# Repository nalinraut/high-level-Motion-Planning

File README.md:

Contributors: GUnnar Horve | Max Merlin | Nishant Doshi | Prakash Bhaskaran | Self.
#IML Internal Repository

by CIBR Lab @ WPI

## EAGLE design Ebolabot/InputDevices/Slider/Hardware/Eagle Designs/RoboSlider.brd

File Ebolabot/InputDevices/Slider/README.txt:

The RoboSlider provides for reading and commanding the position of audio sliders
and buttons, and is specialized for the control of the joint angles any 7 DOF robot.
	*  slider.py -- communicates with RoboSlider devices, allowing for reading and
	   writing slider positions and button states. Also provides easy methods for
	   mapping input and output.
	*  /slider_driver -- contains the Arduino code (and dependent files) for the low
	   level controls of the slider, and for messaging with the computer.
	*  /Hardware -- contains the PCB and enclosure designs for the most recent slider
	   design, and includes a detailed Bill of Materials with links to suppliers.
	*  baxter_slider.py -- utilized the slider module to control Baxter's joint angles
	   with absolute positioning between the slider and Baxter.

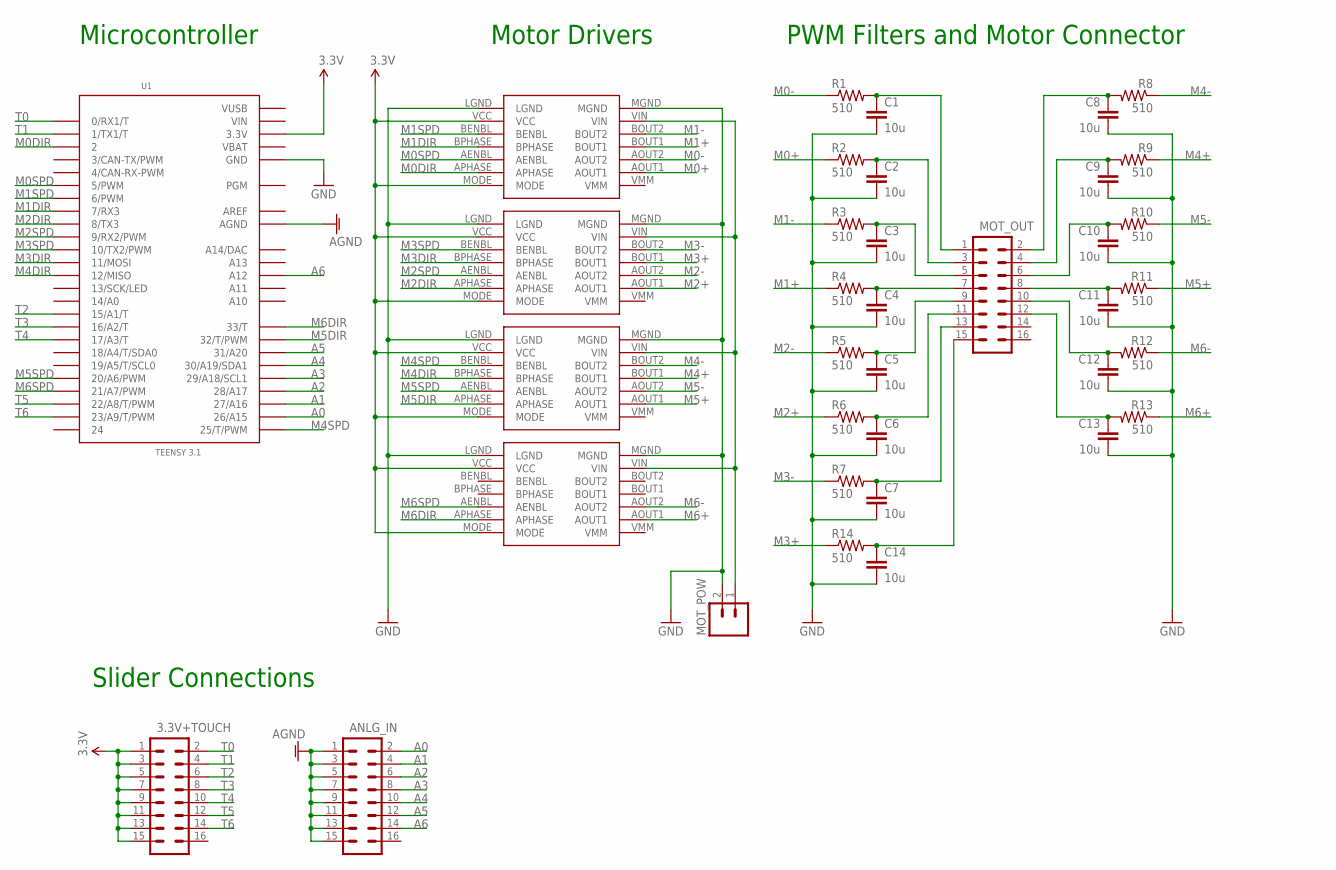
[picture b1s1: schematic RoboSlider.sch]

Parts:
3.3V+TOUCH: M08X2; 2X8
ANLG_IN: M08X2; 2X8
C1, C2, C3, C4, C5, C6, C7, C8, C9, C10, C11, C12, C13, C14: 10u; CAP-PTH-SMALL
MOT_OUT: M08X2; 2X8
MOT_POW: M02PTH; 1X02
R1, R2, R3, R4, R5, R6, R7, R8, R9, R10, R11, R12, R13, R14: 510; AXIAL-0.3
U1: TEENSY 3.1; TEENSY_3.1_ALLPINS
U$1, U$2, U$3, U$4: POLOLU_MOTOR_DRV8835THROUGHHOLE; POLOLU_MOTOR_DRV_DRV8835

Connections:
3.3V: 3.3V+TOUCH.1, 3.3V+TOUCH.3, 3.3V+TOUCH.5, 3.3V+TOUCH.7, 3.3V+TOUCH.9, 3.3V+TOUCH.11, 3.3V+TOUCH.13, 3.3V+TOUCH.15, U1.3.3V, U1.3.3V1 (3.3V), U1.3.3V2 (3.3V), U$1.MODE, U$1.VCC, U$2.MODE, U$2.VCC, U$3.MODE, U$3.VCC, U$4.MODE, U$4.VCC
9V: MOT_POW.1, U$1.VIN, U$2.VIN, U$3.VIN, U$4.VIN
A0: ANLG_IN.2, U1.26 (26/A15)
A1: ANLG_IN.4, U1.27 (27/A16)
A2: ANLG_IN.6, U1.28 (28/A17)
A3: ANLG_IN.8, U1.29 (29/A18/SCL1)
A4: ANLG_IN.10, U1.30 (30/A19/SDA1)
A5: ANLG_IN.12, U1.31 (31/A20)
A6: ANLG_IN.14, U1.A12
AGND: ANLG_IN.1, ANLG_IN.3, ANLG_IN.5, ANLG_IN.7, ANLG_IN.9, ANLG_IN.11, ANLG_IN.13, ANLG_IN.15, U1.AGND
AREF: U1.AREF
GND: C1.2, C2.2, C3.2, C4.2, C5.2, C6.2, C7.2, C8.2, C9.2, C10.2, C11.2, C12.2, C13.2, C14.2, MOT_POW.2, U1.GND, U1.GND1 (GND), U1.GND2 (GND), U$1.LGND, U$1.MGND, U$2.LGND, U$2.MGND, U$3.LGND, U$3.MGND, U$4.LGND, U$4.MGND
M0+: R2.P$1 (1), U$1.AOUT1
M0-: R1.P$1 (1), U$1.AOUT2
M0DIR: U1.2, U$1.APHASE
M0SPD: U1.5 (5/PWM), U$1.AENBL
M1+: R4.P$1 (1), U$1.BOUT1
M1-: R3.P$1 (1), U$1.BOUT2
M1DIR: U1.7 (7/RX3), U$1.BPHASE
M1SPD: U1.6 (6/PWM), U$1.BENBL
M2+: R6.P$1 (1), U$2.AOUT1
M2-: R5.P$1 (1), U$2.AOUT2
M2DIR: U1.8 (8/TX3), U$2.APHASE
M2SPD: U1.9 (9/RX2/PWM), U$2.AENBL
M3+: R14.P$1 (1), U$2.BOUT1
M3-: R7.P$1 (1), U$2.BOUT2
M3DIR: U1.11 (11/MOSI), U$2.BPHASE
M3SPD: U1.10 (10/TX2/PWM), U$2.BENBL
M4+: R9.P$1 (1), U$3.BOUT1
M4-: R8.P$1 (1), U$3.BOUT2
M4DIR: U1.12 (12/MISO), U$3.BPHASE
M4SPD: U1.25 (25/T/PWM), U$3.BENBL
M5+: R11.P$1 (1), U$3.AOUT1
M5-: R10.P$1 (1), U$3.AOUT2
M5DIR: U1.32 (32/T/PWM), U$3.APHASE
M5SPD: U1.20/A6 (20/A6/PWM), U$3.AENBL
M6+: R13.P$1 (1), U$4.AOUT1
M6-: R12.P$1 (1), U$4.AOUT2
M6DIR: U1.33 (33/T), U$4.APHASE
M6SPD: U1.21/A7 (21/A7/PWM), U$4.AENBL
unnamed: C1.1, MOT_OUT.1, R1.P$2 (2)
unnamed: C2.1, MOT_OUT.3, R2.P$2 (2)
unnamed: C3.1, MOT_OUT.5, R3.P$2 (2)
unnamed: C4.1, MOT_OUT.7, R4.P$2 (2)
unnamed: C5.1, MOT_OUT.9, R5.P$2 (2)
unnamed: C6.1, MOT_OUT.11, R6.P$2 (2)
unnamed: C7.1, MOT_OUT.13, R7.P$2 (2)
unnamed: C8.1, MOT_OUT.2, R8.P$2 (2)
unnamed: C9.1, MOT_OUT.4, R9.P$2 (2)
unnamed: C10.1, MOT_OUT.6, R10.P$2 (2)
unnamed: C11.1, MOT_OUT.8, R11.P$2 (2)
unnamed: C12.1, MOT_OUT.10, R12.P$2 (2)
unnamed: C13.1, MOT_OUT.12, R13.P$2 (2)
unnamed: C14.1, MOT_OUT.15, R14.P$2 (2)
T0: 3.3V+TOUCH.2, U1.0 (0/RX1/T)
T1: 3.3V+TOUCH.4, U1.1 (1/TX1/T)
T2: 3.3V+TOUCH.6, U1.15/A1 (15/A1/T)
T3: 3.3V+TOUCH.8, U1.16/A2 (16/A2/T)
T4: 3.3V+TOUCH.10, U1.17/A3 (17/A3/T)
T5: 3.3V+TOUCH.12, U1.22/A8 (22/A8/T/PWM)
T6: 3.3V+TOUCH.14, U1.23/A9 (23/A9/T/PWM)
VBAT: U1.VBAT
VIN: U1.VIN
VUSB: U1.VUSB

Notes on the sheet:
Motor Drivers
Microcontroller
Slider Connections
PWM Filters and Motor Connector

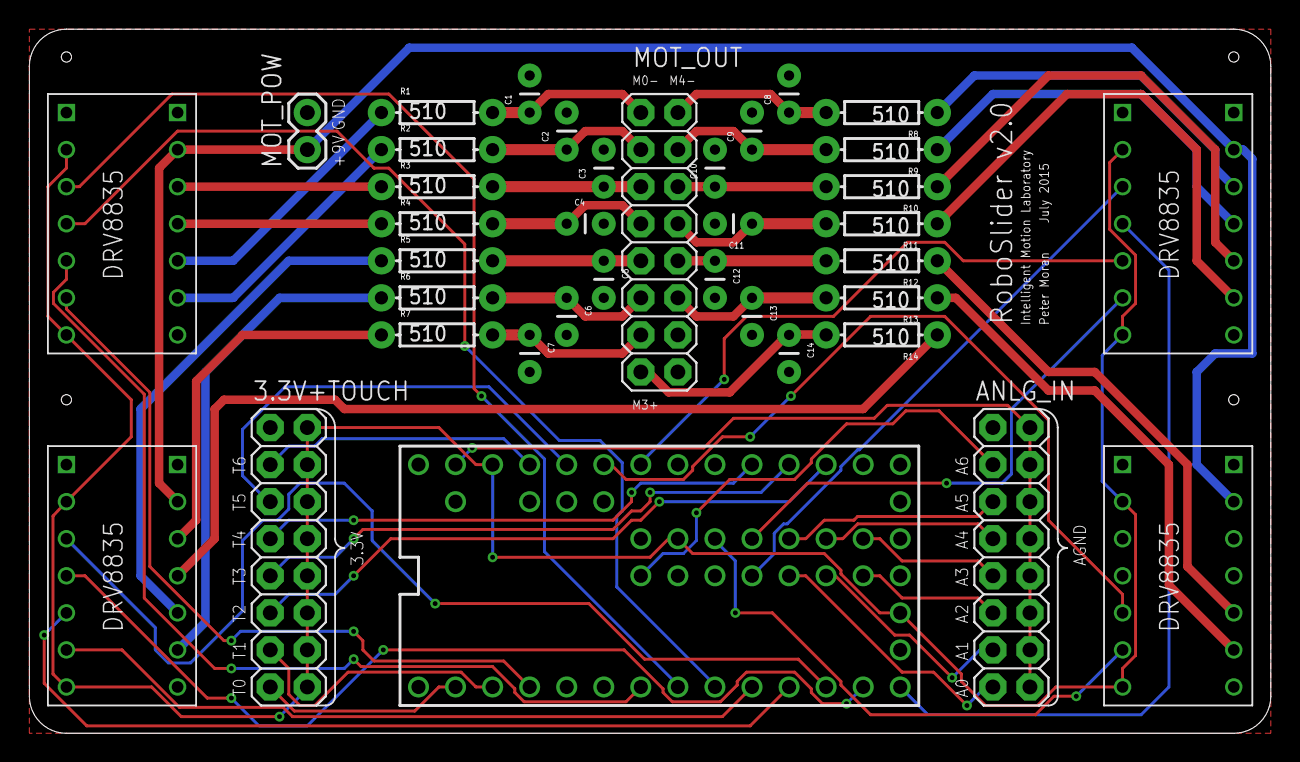
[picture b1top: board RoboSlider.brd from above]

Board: 2 copper layers, 85.1 x 48.2 mm, 37 parts (0 on the bottom side), 60 nets.

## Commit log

2018-04-08 add via uploads
2018-04-09 readme initiated

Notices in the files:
parts and their libraries:
SparkFun-Capacitors: Licensing: Creative Commons ShareAlike 4.0 International - https://creativecommons.org/licenses/by-sa/4.0
